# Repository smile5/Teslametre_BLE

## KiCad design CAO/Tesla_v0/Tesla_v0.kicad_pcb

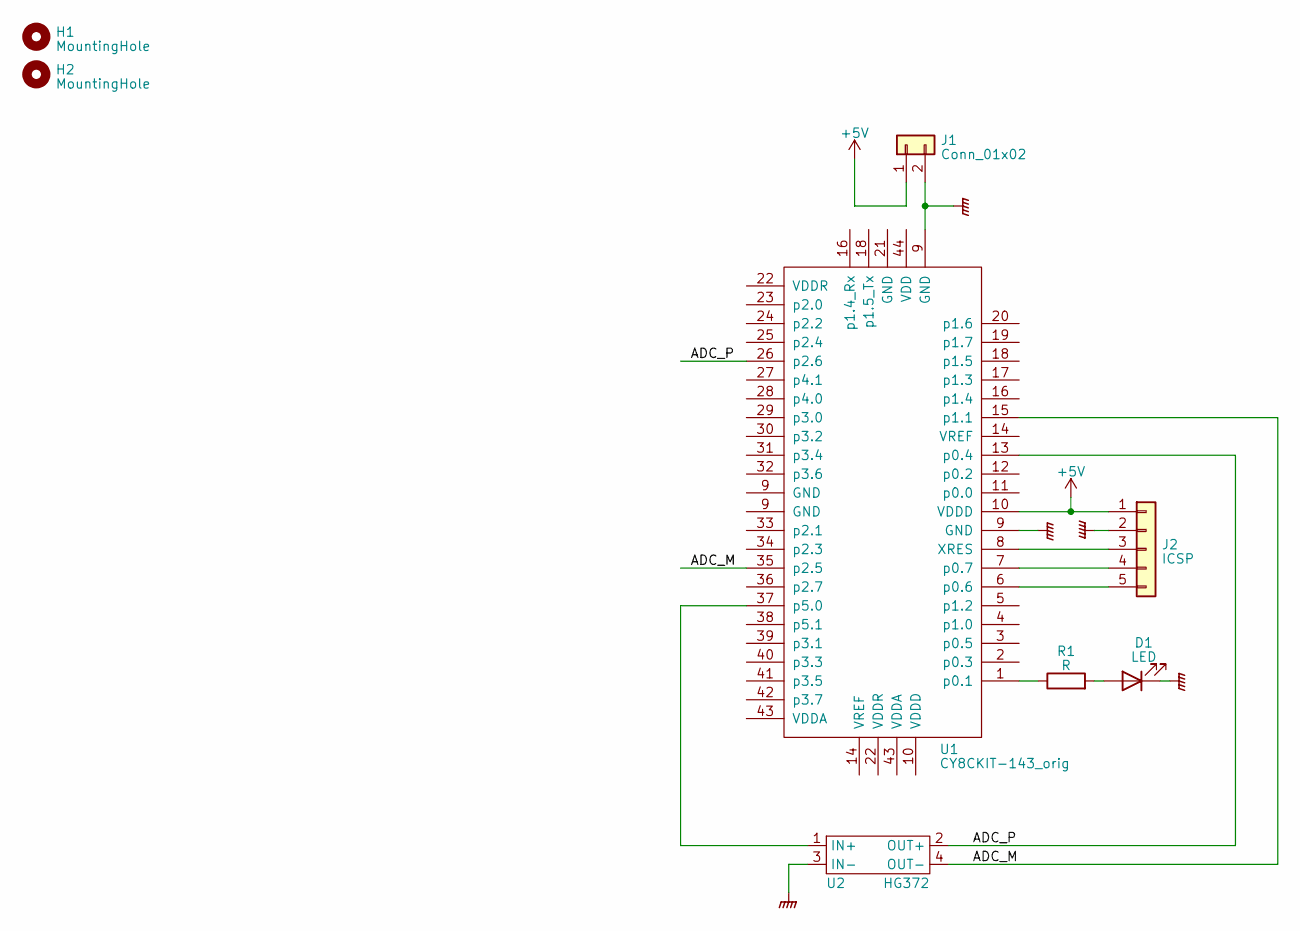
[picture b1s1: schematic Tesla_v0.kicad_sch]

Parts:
D1: LED; LED_D5.0mm
H1, H2: MountingHole; MountingHole_3.2mm_M3_DIN965
J1: Conn_01x02; TerminalBlock_bornier-2_P5.08mm
J2: ICSP; PinHeader_1x05_P2.54mm_Vertical
R1: R; R_Axial_DIN0309_L9.0mm_D3.2mm_P5.08mm_Vertical
U1: CY8CKIT-143_orig; CY8CKIT-143-2
U2: HG372; HG372A_2

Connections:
+5V: J1.1, J2.1, U1.10 (VDDD)
/ADC_M: U1.15 (p1.1), U1.35 (p2.5), U2.4 (OUT-)
/ADC_P: U1.13 (p0.4), U1.26 (p2.6), U2.2 (OUT+)
GNDPWR: D1.1 (K), J1.2, J2.2, U1.9 (GND), U2.3 (IN-)
unnamed: D1.2 (A), R1.2
unnamed: J2.3, U1.8 (XRES)
unnamed: J2.4, U1.7 (p0.7)
unnamed: J2.5, U1.6 (p0.6)
unnamed: R1.1, U1.1 (p0.1)
unnamed: U1.37 (p5.0), U2.1 (IN+)

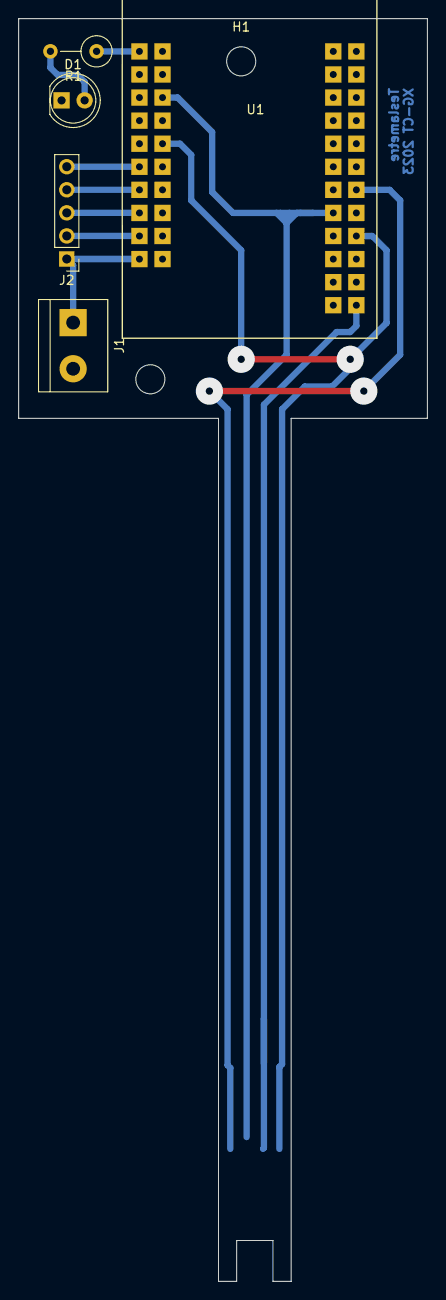
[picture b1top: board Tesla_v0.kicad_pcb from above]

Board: 2 copper layers, 45.0 x 139.0 mm, 8 parts (1 on the bottom side), 10 nets.
